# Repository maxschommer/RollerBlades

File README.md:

# RollerBlades
Roller blade PCBs

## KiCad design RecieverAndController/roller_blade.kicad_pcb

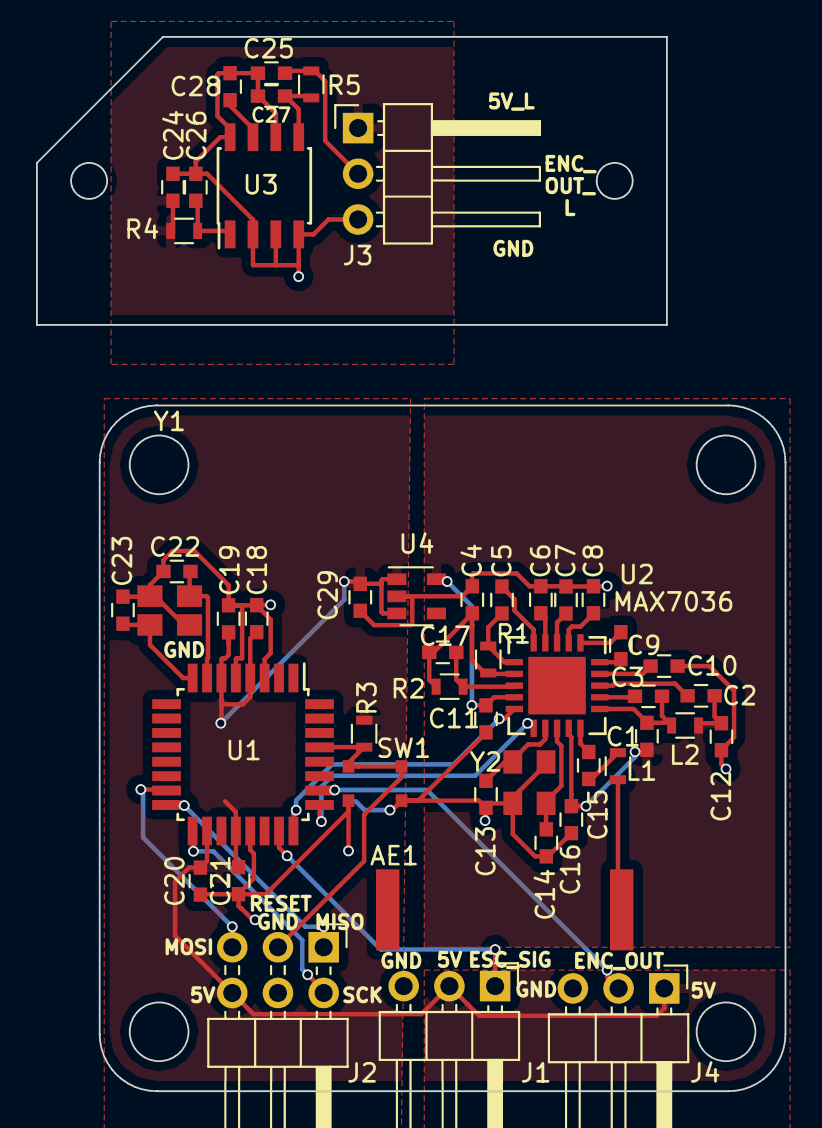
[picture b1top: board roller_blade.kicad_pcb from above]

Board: 2 copper layers, 38.1 x 38.1 mm, 48 parts (0 on the bottom side), 36 nets.

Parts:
AE1: Antenna; 311-1570-1-ND
C1: 2.7pF; C_0603
C2, C3, C15: 100pF; C_0603
C4, C11, C16, C17: .1uF; C_0603
C5: 390pF; C_0603
C6: 180pF; C_0603
C7, C29: 1uF; C_0603
C8: .01uF; C_0603
C9: 22pF; C_0603
C10, C13, C14: 10pF; C_0603
C12: 220pF; C_0603
C18, C19, C20, C21, C26, C27, C28: 100nF; C_0603
C22, C23: 18pF; C_0603
C24, C25: 1nF; C_0603
J1, J3, J4: Conn_01x03; Pin_Header_Angled_1x03_Pitch2.54mm
J2: Conn_02x03_Counter_Clockwise; Pin_Header_Angled_2x03_Pitch2.54mm
L1: 47nH; L_0603
L2: 15nH; L_0603
R1: 22kOHM; R_0603
R2: 220kOhm; R_0603
R3: 10k; R_0603
R4: 10; R_0603
R5: 50; R_0603
SW1: SW_DIP_x01; CKN10291CT-ND
U1: ATMEGA328-AU; TQFP-32_7x7mm_Pitch0.8mm
U2: MAX7036; MAX7036GTP
U3: MLX90365; SOIC-8_3.9x4.9mm_Pitch1.27mm
U4: AP2204_3V3; SOT-23-5
Y1: 16MHz; SER3686DKR-ND
Y2: 13.56MHz; 1253-1737-1-ND

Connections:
+3V3: C1.2, C2.2, C8.2, C11.1, C12.1, C16.1, L2.1, U2.4, U2.12, U2.19, U4.5
+5V: C18.1, C19.1, C20.1, C21.1, C29.1, J1.2, J2.6, J4.1, R3.1, U1.4, U1.6, U1.18, U1.20, U4.1, U4.3
/ENC_OUT: J4.2, U1.26
/ESC_SIG: J1.1, U1.23
/MCU/MISO: J2.1, U1.16
/MCU/MOSI: J2.5, U1.15
/MCU/RESET: J2.3, R3.2, SW1.1, U1.29
/MCU/SCK: J2.2, U1.17
/REC_EN: U1.25, U2.1
/REC_OUT: U1.24, U2.20
/encoder/5V_L: C24.1, J3.1, R4.2
/encoder/ENC_OUT_L: C25.2, J3.2, R5.2
/encoder/GND_L: C24.2, C25.1, C26.2, C27.1, C28.2, J3.3, U3.2, U3.3, U3.4, U3.6, U3.8
GND: C4.2, C6.2, C7.2, C8.1, C10.2, C11.2, C12.2, C13.2, C14.2, C16.2, C18.2, C19.2, C20.2, C21.2, C22.1, C23.1, C29.2, J1.3, J2.4, J4.3, SW1.2, U1.3, U1.5, U1.21, U4.2, Y1.2, Y1.4, Y2.2, Y2.4
unnamed: AE1.1, L1.1
unnamed: C1.1, C3.2, L2.2, U2.6
unnamed: C2.1, U2.8
unnamed: C3.1, U2.7
unnamed: C5.1, U2.15
unnamed: C5.2, R1.2, U2.16
unnamed: C6.1, U2.14
unnamed: C7.1, U2.13
unnamed: C9.1, U2.10
unnamed: C9.2, U2.11
unnamed: C10.1, U2.9
unnamed: C13.1, U2.2, Y2.1
unnamed: C14.1, U2.3, Y2.3
unnamed: C15.1, U2.5
unnamed: C15.2, L1.2
unnamed: C4.1, C17.1, R1.1, R2.1, U2.17
unnamed: C17.2, R2.2, U2.18
unnamed: C22.2, U1.7, Y1.1
unnamed: C23.2, U1.8, Y1.3
unnamed: C26.1, R4.1, U3.1
unnamed: C27.2, R5.1, U3.5
unnamed: C28.1, U3.7

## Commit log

2018-03-03 Added microcontroller sheet
2018-03-03 adding custom components
2018-03-03 Did power and encoder
2018-03-03 commiting reciever
2018-03-03 Fixed merge conflicts for real
2018-04-07 commiting custom pretty
2018-04-07 adding blade pcbs
2018-04-07 Making stuff betteR
2018-04-07 adding blade connector pcb
2018-04-08 Finished schematic
2018-04-08 did easy stuff
2018-04-08 adding gerber files
2018-04-08 adding footprints to schematic
2018-04-08 Waiting for the merge conflict storm
2018-04-09 adding start of pcb
2018-04-09 adding footprints
2018-04-09 Finished transmitter
2018-04-09 adding and fixing reciever
2018-04-11 adding gerber files without dxf

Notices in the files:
parts and their libraries:
Copyright 2016 Accelerated Designs. All rights reserved.
